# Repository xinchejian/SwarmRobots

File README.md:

xcj_swarm
=========

Xinchejian Swarm Robot project

Introduction:

Build a swarm of robots with autonomus behavior to achieve their goals by interacting with each other using IR communication.

See each xinCheJian wiki for assembly instructions and information.

Original Requirements:
  Each basic robot contains the following:
	- 1x microcontroller Attiny2313
	- 1x motor controller L293D
	- 2x gear motors
	- 1x LiPo battery 3.7V
	Sensor shield

A custom made PCB will be used. This PCB will be mounted into a 3D printed casing which contains the gear motors and the wheels as well the IR sensor array.

Goal is that the maximum price for the basic robot should not exceed 5US$ (without shield)

Each robot will have a basic programming and basic hardware platform. 
The basic programming is:
1. Self protection: 
	- check your battery status
	- find the charging station when battery runs low
	- avoid obstacles and other robots
	- search for power (sunlight etc.)
2. Community (swarm) needs:
	- search for building material
	- search for dead robots
	- bring dead robots to the charging station
	- help dead robots with a charger robot
	- tell others where to find power (sunlight)
	- tell others where is an obstacle or danger

Folder structure:
	/32u4-edwardrf	work in progress - check XCJ mailing list for later versions.
	/AtTiny2313	AtTiny2313 version - that won the AFRON competition
	/ATMEGA328	version based on 
	/ATMEGA168	latest super version (replaces UNO version).

	Note there is a LARGE amount of direct compatability between the code for ALL versions. Differences to note are:
		- different IO pins - see "Arduino, AtTiny, L293 and header pin mappings.ods"
		- size of memory limits size of code
		- AtTiny versions have fewer IO commands available. See http://wiki.xinchejian.com/wiki/Programming-AFRON

Branches & master
	- Please use branches to do YOUR work before committing back to the master!
	- Goal is for the master to be 'production ready' at ALL TIMES!

More at the XinCheJian website wiki.xinchejian.com 
	- the original Swarmrobot pages at http://wiki.xinchejian.com/wiki/Swarm_robots
	- collated summary and AFRON competition entry
	http://wiki.xinchejian.com/wiki/Category:AFRON_$10_Robot_Competition

	latest Swarmrobot index - entry page is now: http://wiki.xinchejian.com/wiki/Category:Swarm_Robots

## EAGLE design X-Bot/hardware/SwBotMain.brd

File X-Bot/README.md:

简介：
   X-Bot是一款群体机器人（Swarm Robot），让这样一群小巧的机器人来实现蚁群可以完成的任务，这就是群体机器人。它由来自新车间（xinchejian.com）创客空间成员组建的一个小组创建。该机器人是基于红外线传感而制作的，它的特点是低成本、易于实践和多功能。该机器人初级版在2012年9月 “AFRON $10 robot challenge” 上获得常规组的第二名。
   该项目有Lutz提议建立，于2012年4月启动，其目的是让成员通过实践可以学到多样的技能，并促进人之间的交流。该目的通过构建个体功能很简单，但通过它们之间的合作可以完成复杂任务的小机器人来实现，这就是Swarm Robot。
该项目在进行中，核心成员为：
   Lutz Michaelis： 德国 （发起人）
   Spencer F：澳大利亚
   Edward Jiang： 中国
   Sunny Sun ：中国
   Leo Yan ： 中国

   在这里归档是LeoYan在其基础上的进一步发展的中级版本，采用了ATMEGA328，拥有更大的创作空间，通过您的加入将会使其功能更完善，也将形成一个圈子，一起交流，一起make stuff。

版权声明：
    所有文档和硬件设计采用：CC BY-NC 3.0 CN ， see <http://creativecommons.net.cn/licenses>
    所有软件代码采用      ：GPL3.0 ，          see <http://www.gnu.org/licenses/>

# English

## Programming

* Checkout and compile the log
 * Set target to Arduino Uno
 * symlink source to SwarmRobot (required by Arduino IDE projects)
* Charge the X-Bot fully
* Configure your X-Bot ID in Swbot.Config.h
 * If you want to start _START_REMOTE_CONTROL
 * Select the behavior you want

```
  #define ROBOT_TYPE_ANT  0x10 (food hunter)
  #define ROBOT_TYPE_ANT_LINEUP 0x11 (line up to and follow the higher id)
  #define ROBOT_TYPE_FOOD 0x21 (turns your X-Bot into a edible source of food)
```
 * Verify the program (compilation step)
* Connect the USB TTL Programmer v2 to your USB
 * Align VCC to VCC
* Upload, should end up with Arduino 1.0.1:

```
avrdude done.  Thank you.
```

## Details

## Behavior changes

In Action.cpp, behavior is defined in RuleTbl as a state machine.

Below, an example using the food hunter behavior:

This represents the current state and the action to do (internal state):

    {INTERIORINFO, TASK_STAGE, TS_LOOKING,  0, 0, 0,  true},

The action is activated under each state by ANYINFO:

    {ANYINFO, 0, 0,  ACTION_IN_SET, TASK_STAGE, TS_LOOKING,  false },

(last boolean is used to create a linked-list of actions to be done following a state)

The first 3 parameters define the conditional for an action... In the case of ANYINFO, there's no conditional so parameters are zero:

    {ANYINFO, 0, 0,  ACTION_EXT_LED, LED_MODE_MANUAL, 0B00,  true},

If the type of message is FOOD, the action is to set the internal variable target to true and keep target id

    {ROBOTINFO_TYPE, ROBOT_ID_ANY, ROBOT_TYPE_FOOD,  ACTION_IN_SET, TARGET, INFO_STATE_SET,  true},

If the TARGET variable is set, then change the state to TS_FOUND:

    {INTERIORINFO, TARGET, INFO_STATE_SET,  ACTION_IN_SET, TASK_STAGE, TS_FOUND,  false},

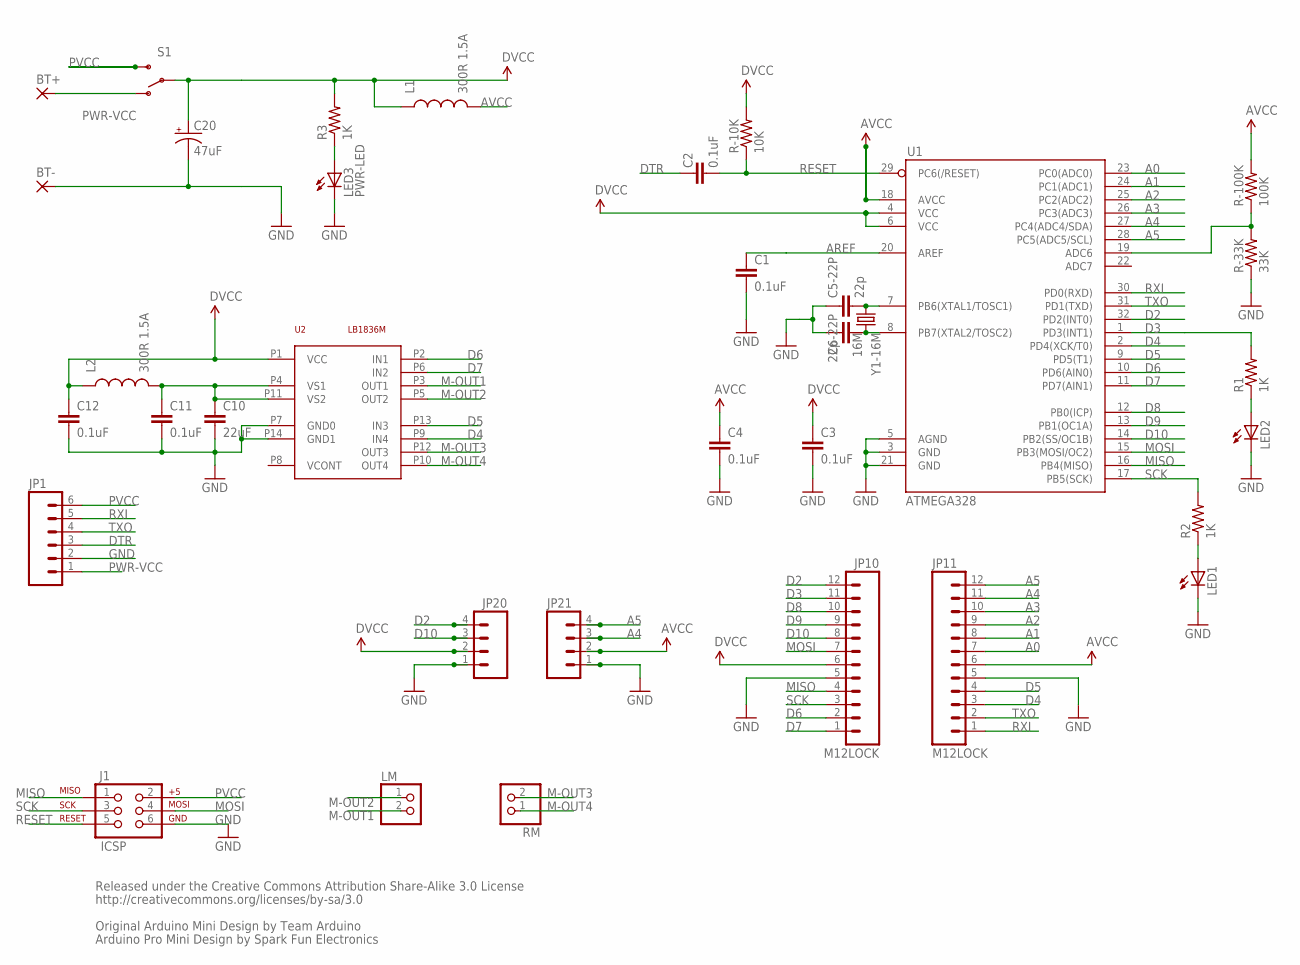
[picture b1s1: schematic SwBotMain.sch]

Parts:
BT+: SMD2; SMD1,27-2,54
BT-: SMD2; SMD1,27-2,54
C1, C2, C3, C4, C11, C12: 0.1uF; 0805
C5-22P, C6-22P: 22p; 0805
C10: 22uF; 1206
C20: 47uF; EIA3528
J1: ICSP; 2X3_LOCK
JP1: M06LOCK; 1X06_LOCK
JP10, JP11: M12LOCK; 1X12_LOCK
JP20, JP21: M04LOCK_LONGPADS; 1X04_LOCK_LONGPADS
L1, L2: 300R 1.5A; 0805
LED1, LED2: LEDCHIP-LED0805; CHIP-LED0805
LED3: PWR-LED; LED5MM
LM: PINHD-1X2; 1X02
R1, R2, R3: 1K; 0805
R-10K: 10K; 0805
R-33K: 33K; 0805
R-100K: 100K; 0805
RM: PINHD-1X2; 1X02
S1: SWITCH-SPDTPTH_LOCK; SWITCH-SPDT_LOCK.007S
U1: ATMEGA328; TQFP32-08
U2: LB1836M; MFP14S
Y1-16M: 16M; CRYSTAL-TXC-7A

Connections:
A0: JP11.7, U1.23 (PC0(ADC0))
A1: JP11.8, U1.24 (PC1(ADC1))
A2: JP11.9, U1.25 (PC2(ADC2))
A3: JP11.10, U1.26 (PC3(ADC3))
A4: JP11.11, JP21.3, U1.27 (PC4(ADC4/SDA))
A5: JP11.12, JP21.4, U1.28 (PC5(ADC5/SCL))
AREF: C1.1, U1.20 (AREF)
AVCC: C4.1, JP11.6, JP21.2, L1.2, R-100K.2, U1.18 (AVCC)
D2: JP10.12, JP20.4, U1.32 (PD2(INT0))
D3: JP10.11, R1.2, U1.1 (PD3(INT1))
D4: JP11.3, U1.2 (PD4(XCK/T0)), U2.P9 (IN4)
D5: JP11.4, U1.9 (PD5(T1)), U2.P13 (IN3)
D6: JP10.2, U1.10 (PD6(AIN0)), U2.P2 (IN1)
D7: JP10.1, U1.11 (PD7(AIN1)), U2.P6 (IN2)
D8: JP10.10, U1.12 (PB0(ICP))
D9: JP10.9, U1.13 (PB1(OC1A))
D10: JP10.8, JP20.3, U1.14 (PB2(SS/OC1B))
DTR: C2.2, JP1.3
DVCC: C3.1, C12.1, C20.A (+), JP10.6, JP20.2, L1.1, L2.1, R3.2, R-10K.2, S1.2, U1.4 (VCC), U1.6 (VCC), U2.P1 (VCC)
GND: BT-.1, C1.2, C3.2, C4.2, C5-22P.1, C6-22P.2, C10.2, C11.2, C12.2, C20.C (-), J1.6, JP1.2, JP10.5, JP11.5, JP20.1, JP21.1, LED1.C, LED2.C, LED3.K (C), R-33K.1, U1.3 (GND), U1.5 (AGND), U1.21 (GND), U2.P7 (GND0), U2.P14 (GND1)
M-OUT1: LM.2, U2.P3 (OUT1)
M-OUT2: LM.1, U2.P5 (OUT2)
M-OUT3: RM.2, U2.P12 (OUT3)
M-OUT4: RM.1, U2.P10 (OUT4)
MISO: J1.1, JP10.4, U1.16 (PB4(MISO))
MOSI: J1.4, JP10.7, U1.15 (PB3(MOSI/OC2))
unnamed: C6-22P.1, U1.8 (PB7(XTAL2/TOSC2)), Y1-16M.P$2 (2)
unnamed: C5-22P.2, U1.7 (PB6(XTAL1/TOSC1)), Y1-16M.P$1 (1)
unnamed: LED2.A, R1.1
unnamed: LED3.A, R3.1
unnamed: C10.1, C11.1, L2.2, U2.P4 (VS1), U2.P11 (VS2)
unnamed: R-33K.2, R-100K.1, U1.19 (ADC6)
unnamed: LED1.A, R2.1
PVCC: J1.2, JP1.6, S1.3 (S)
PWR-VCC: BT+.1, JP1.1, S1.1 (O)
RESET: C2.1, J1.5, R-10K.1, U1.29 (PC6(/RESET))
RXI: JP1.5, JP11.1, U1.30 (PD0(RXD))
SCK: J1.3, JP10.3, R2.2, U1.17 (PB5(SCK))
TXO: JP1.4, JP11.2, U1.31 (PD1(TXD))

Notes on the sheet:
Released under the Creative Commons Attribution Share-Alike 3.0 License
http://creativecommons.org/licenses/by-sa/3.0
Original Arduino Mini Design by Team Arduino
Arduino Pro Mini Design by Spark Fun Electronics

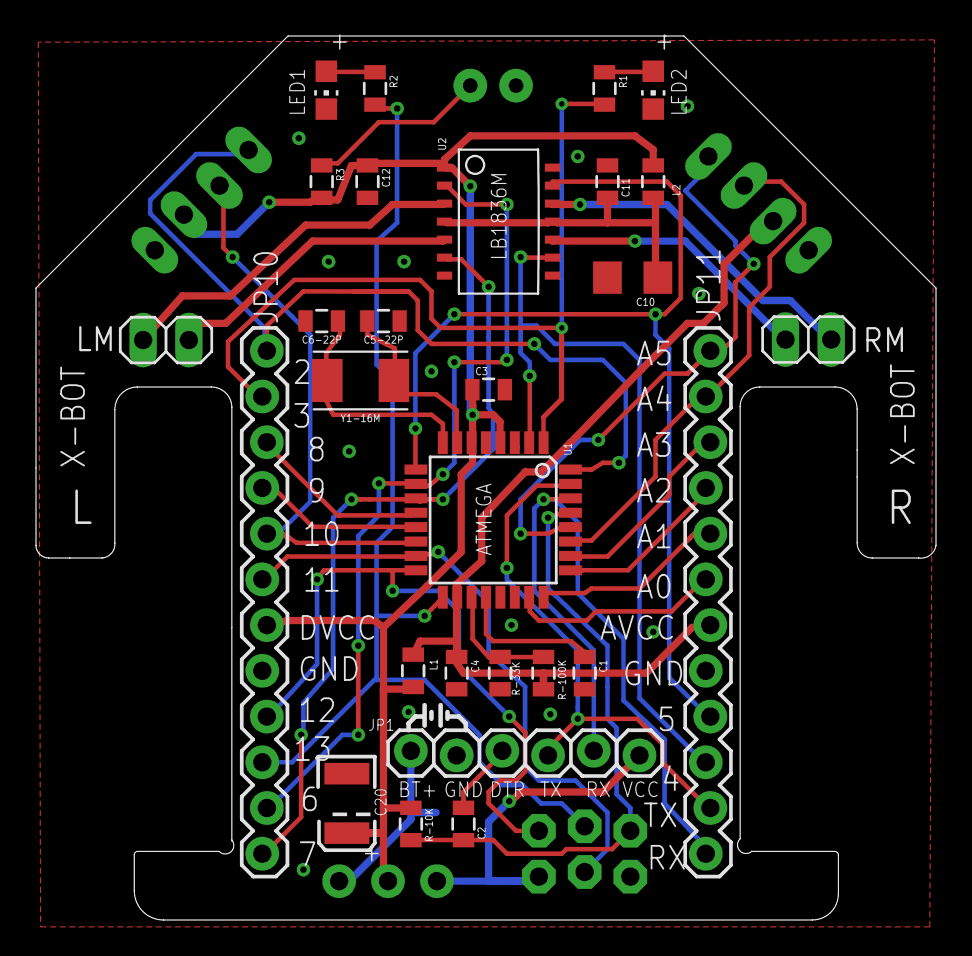
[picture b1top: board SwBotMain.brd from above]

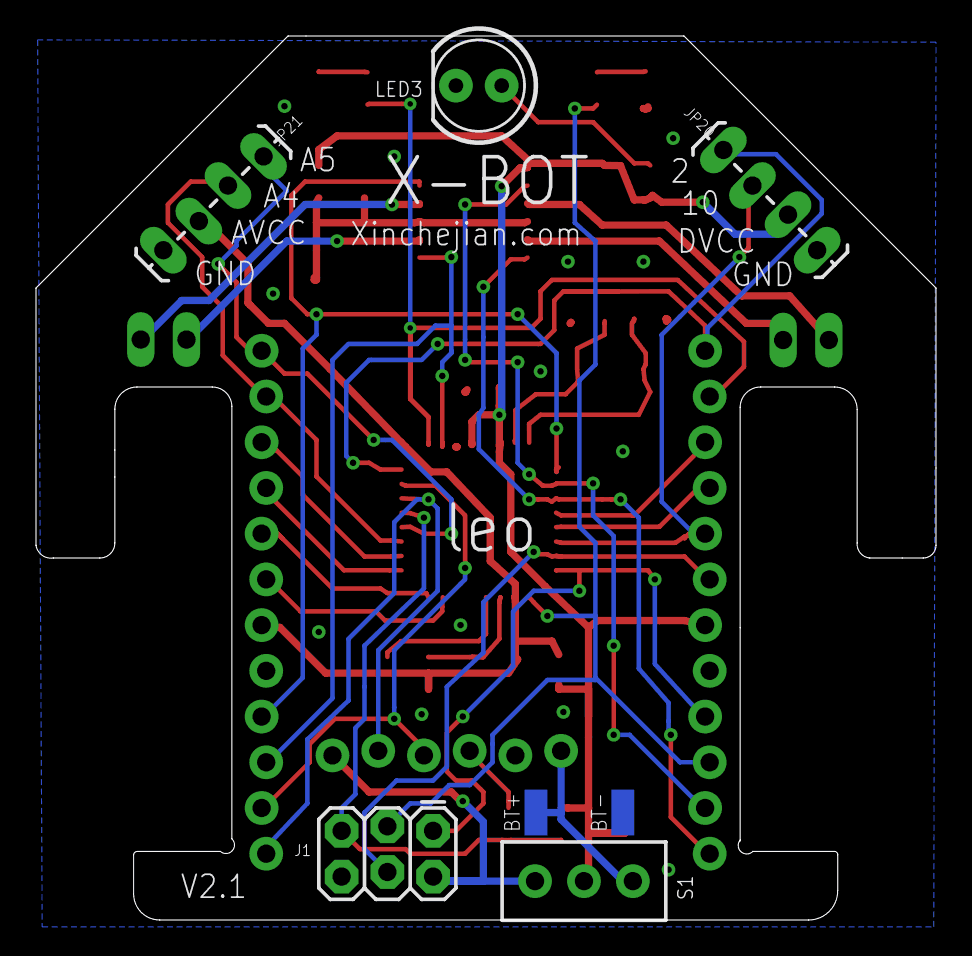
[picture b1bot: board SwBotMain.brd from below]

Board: 2 copper layers, 50.0 x 49.1 mm, 35 parts (7 on the bottom side), 39 nets.

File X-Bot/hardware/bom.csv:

名称;Item;Package;Type;Quantity
MCU;MCU;TQFP;ATMEGA328P-AU;1
电机驱动;MOTOR DRIVER;MFP14S;LB1836M;1
晶振;CRISTAL; EIA3528 (TXC-7A);16M;1
大电流磁珠;Ferrite bead;0805;大电流磁珠 300R 1.5A;2
红外发射管;IR-LED ;5mm;IR-LED;1
一体化红外接收管;IR-RECEIVER ;TSOP;NJL21V400A;4
LED;LED;0805;green;2
LED;LED;0805;orange;4
LED;LED;5mm;red LED 红色;1
排针;Pin header;间距2.54mm 针长12mm;1X40;0.5
排针;Pin header;间距2.54mm  针长12mm;2X40;0.1
排针;Pin header;间距2.54mm;90度 1X40;0.2
排母;Pin socket;2.54mm;1X08;3
排母;Pin socket;2.54mm;1X12;2
电阻;resistor;0805;100K  (1/100precision);1
电阻;resistor;0805;33K (1/100precision);1
电阻;resistor;0805;1k;7
电阻;resistor;0805;150R;2
电阻;resistor;0805;10K;1
电阻;resistor;0805;47R;4
瓷电容;capacitor;0805;0.1uF;6
瓷电容;capacitor;0805;22p;2
瓷电容;capacitor;1206;22uF;5
钽电容;tantalum capacitor;EIA3528;47uF;1
带保护板锂电池;Li Battery ;Larger than 180mA;3cmX2cm;1
小拨动开关;小拨动开关;8mm*4mm 柄5mm;SS-12D0;1
Motor 微型直流减速电机;Motor 微型直流减速电机;;J9xx;2
Screw 平头螺丝;Screw 平头螺丝;;M2*8;2
wheel 皮带轮;wheel 皮带轮;橙色或白色;17*4*1.9;2
垫片;垫片;O型;inter diameter 2.5 mm;2
O型圈密封圈;O型圈密封圈;;外径15，线径2;2
硬纸片;Card board;30mmX30mm; 比如牙膏包装盒，不透光;1

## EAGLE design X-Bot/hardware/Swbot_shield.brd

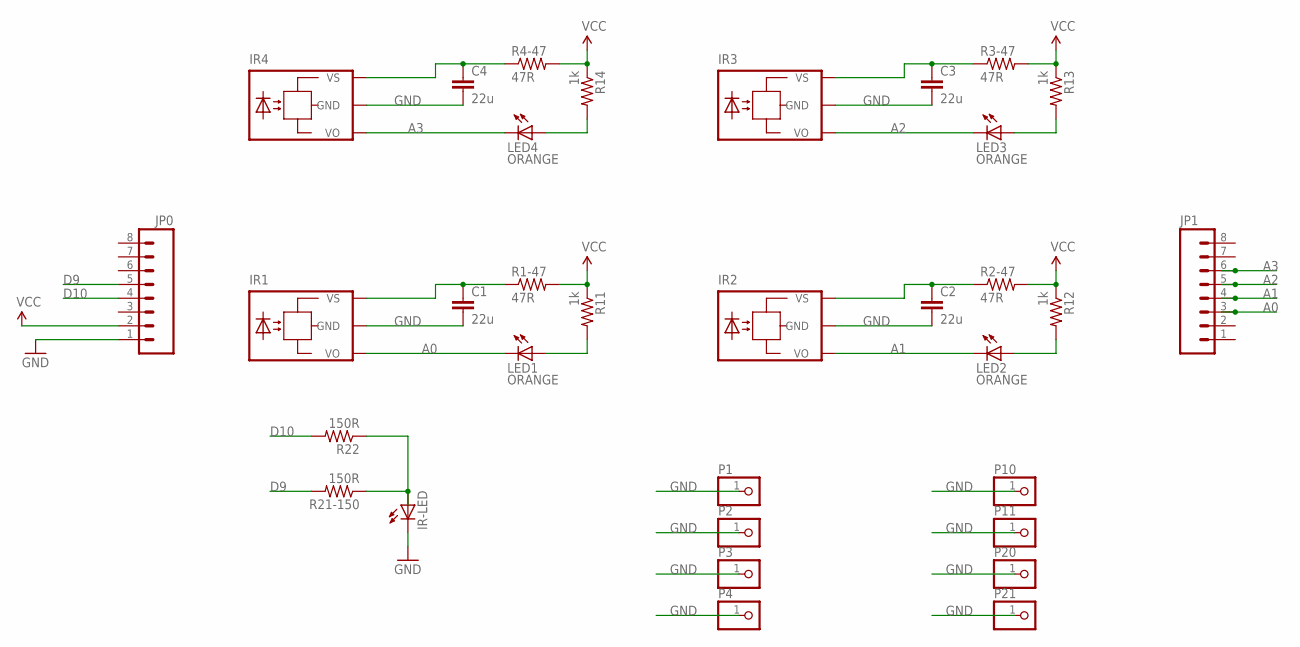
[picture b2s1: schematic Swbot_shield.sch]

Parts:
C1, C2, C3, C4: 22u; 1206
IR1, IR2, IR3, IR4: -NJL; TSOP
IR-LED: LED5MM
JP0, JP1: M08LOCK; 1X08_LOCK
LED1, LED2, LED3, LED4: ORANGE; CHIPLED_0805
P1, P2, P3, P4, P10, P11, P20, P21: PINHD-1X1; 1X01
R1-47, R2-47, R3-47, R4-47: 47R; 0805
R11, R12, R13, R14: 1k; 0805
R21-150, R22: 150R; 0805

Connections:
A0: IR1.VO, JP1.3, LED1.C
A1: IR2.VO, JP1.4, LED2.C
A2: IR3.VO, JP1.5, LED3.C
A3: IR4.VO, JP1.6, LED4.C
D9: JP0.5, R21-150.2
D10: JP0.4, R22.2
GND: C1.2, C2.2, C3.2, C4.2, IR1.GND, IR2.GND, IR3.GND, IR4.GND, IR-LED.K (C), JP0.1, P1.1, P2.1, P3.1, P4.1, P10.1, P11.1, P20.1, P21.1
unnamed: LED1.A, R11.2
unnamed: IR-LED.A, R21-150.1, R22.1
unnamed: LED2.A, R12.2
unnamed: LED3.A, R13.2
unnamed: C2.1, IR2.VCC (VS), R2-47.1
unnamed: LED4.A, R14.2
unnamed: C4.1, IR4.VCC (VS), R4-47.1
unnamed: C3.1, IR3.VCC (VS), R3-47.1
unnamed: C1.1, IR1.VCC (VS), R1-47.1
VCC: JP0.2, R1-47.2, R2-47.2, R3-47.2, R4-47.2, R11.1, R12.1, R13.1, R14.1

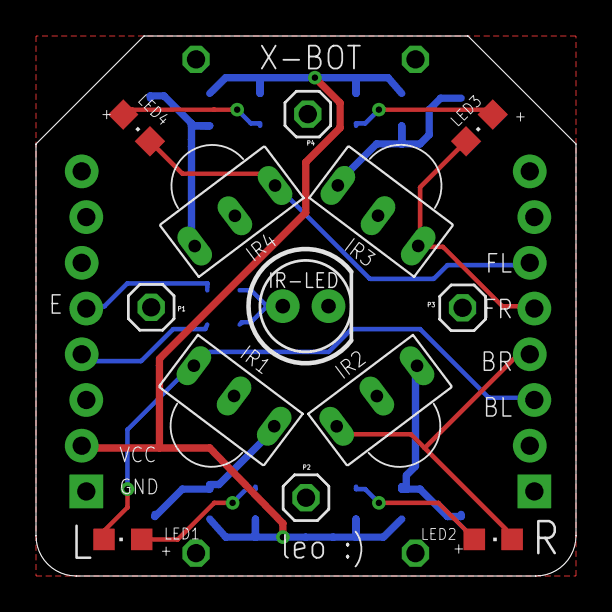
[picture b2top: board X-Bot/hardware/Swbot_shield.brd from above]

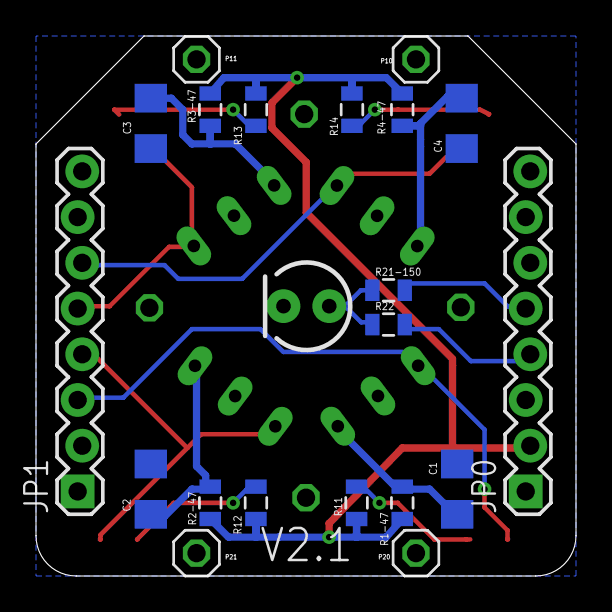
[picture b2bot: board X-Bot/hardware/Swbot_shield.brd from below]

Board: 2 copper layers, 30.0 x 30.0 mm, 33 parts (20 on the bottom side), 17 nets.

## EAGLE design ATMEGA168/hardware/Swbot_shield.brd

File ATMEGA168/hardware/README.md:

xcj_swarm
=========

Xinchejian Swarm Robot project

Introduction:

Build a swarm of robots with autonomus behavior to achieve their goals by interacting with each other using IR communication.

Requirements:

Each basic robot contains the following:
	
	- 1x microcontroller Attiny2313
	- 1x motor controller L293D
	- 2x gear motors
	- 1x LiPo battery 3.7V
	Sensor shield

A custom made PCB will be used. This PCB will be mounted into a 3D printed casing which contains the gear motors and the wheels as well the IR sensor array.

Goal is that the maximum price for the basic robot should not exceed 5US$ (without shield)

Each robot will have a basic programming and basic hardware platform. 
The basic programming is:

1. Self protection: 
	- check your battery status
	- find the charging station when battery runs low
	- avoid obstacles and other robots
	- search for power (sunlight etc.)
2. Community (swarm) needs:
	- search for building material
	- search for dead robots
	- bring dead robots to the charging station
	- help dead robots with a charger robot
	- tell others where to find power (sunlight)
	- tell others where is an obstacle or danger

Folder structure:

	/kicad 		AtTin2313 - kicad schematics and PCB design files
	/source		AtTin2313 - source code

	/ATMEGA328	version based on 
	/UNO		version built onto and existing Arduino UNO.

	Note there is a LARGE amount of direct compatability between the code for ALL versions. Differences to note are:
		- different IO pins - see "Arduino, AtTiny, L293 and header pin mappings.ods"
		- size of memory limits size of code
		- AtTiny versions have fewer IO commands available. See http://wiki.xinchejian.com/wiki/Programming-AFRON

Branches & master
	- Please use branches to do YOUR work before committing back to the master!
	- Goal is for the master to be 'production ready' at ALL TIMES!

Sample Git info:
    http://kentnguyen.com/development/visualized-git-practices-for-team/
    http://gitref.org/branching/
    http://marklodato.github.com/visual-git-guide/index-en.html
    http://think-like-a-git.net/
    https://github.com/diaspora/diaspora/wiki/Git-Workflow

More at the XinCheJian website wiki.xinchejian.com 
	- the original Swarmrobot pages at http://wiki.xinchejian.com/wiki/Swarm_robots
	- collated summary and AFRON competition entry
		 - URL not yet published, but after 15/9/2012 you will find it via 
				http://wiki.xinchejian.com/wiki/Category:AFRON_$10_Robot_Competition

************************************************************
Changes made to move from previous mess to this structure:-

/swarmIR		-> AtTiny2313/hardware/swarmIRShield
/kicad			-> AtTiny2313/hardware/mainPCB

/source-Avoid-Follow	-> AtTiny2313/software/SwitchShield_Avoid_Follow 
/source-IR		-> AtTiny2313/software/IR_Follow_AFRON
/swarm_wall_follow_ir	-> AtTiny2313/software/IR_object_detection

All the Arduino code files also renamed so can open sketches in the folder!

************************************************************

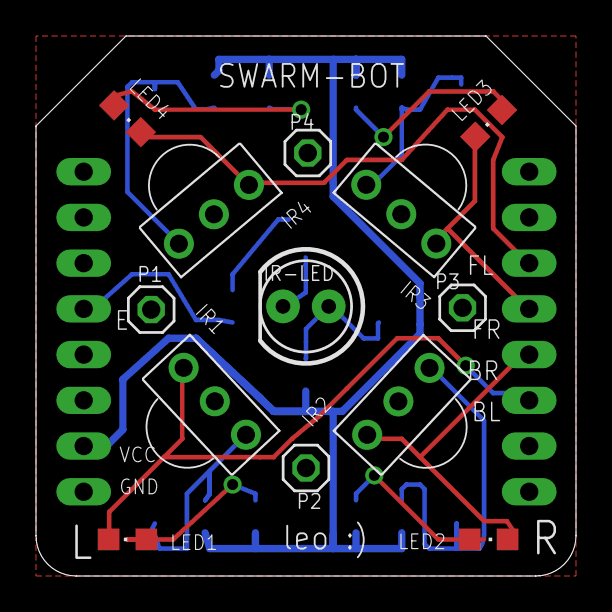
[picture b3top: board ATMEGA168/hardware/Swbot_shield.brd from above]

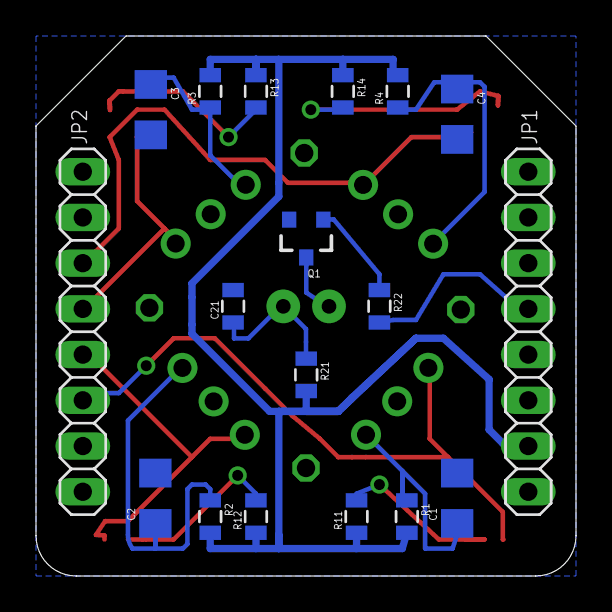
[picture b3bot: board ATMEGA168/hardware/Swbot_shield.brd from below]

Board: 2 copper layers, 30.0 x 30.0 mm, 31 parts (18 on the bottom side), 18 nets.

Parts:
C1, C2, C3, C4: 22u; 1206
C21: 0.1u; 0805
IR1, IR2, IR3, IR4: TSOP
IR-LED: LED5MM
JP1, JP2: 1X08
LED1, LED2, LED3, LED4: ORANGE; CHIPLED_0805
P1, P2, P3, P4: 1X01
Q1: S9013; SOT23-3
R1, R2, R3, R4, R21: 47R; 0805
R11, R12, R13, R14: 1k; 0805
R22: 220R; 0805

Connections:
A0: IR1.VO, JP2.3, LED1.C
A1: IR2.VO, JP2.4, LED2.C
A2: IR3.VO, JP2.5, LED3.C
A3: IR4.VO, JP2.6, LED4.C
D9: JP1.5, R22.2
GND: C1.2, C2.2, C3.2, C4.2, C21.2, IR1.GND, IR2.GND, IR3.GND, IR4.GND, JP1.1, P1.1, P2.1, P3.1, P4.1, Q1.2
unnamed: LED1.A, R11.2
unnamed: C21.1, IR-LED.A, R21.1
unnamed: IR-LED.K, Q1.3
unnamed: LED2.A, R12.2
unnamed: Q1.1, R22.1
unnamed: LED3.A, R13.2
unnamed: C2.1, IR2.VCC, R2.1
unnamed: LED4.A, R14.2
unnamed: C4.1, IR4.VCC, R4.1
unnamed: C3.1, IR3.VCC, R3.1
unnamed: C1.1, IR1.VCC, R1.1
VCC: JP1.2, R1.2, R2.2, R3.2, R4.2, R11.1, R12.1, R13.1, R14.1, R21.2

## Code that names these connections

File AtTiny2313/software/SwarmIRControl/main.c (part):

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#endif

// These pins receive signals from the IR LEDs
#define IR_FC PD4              // IR LED Front Center
#define IR_R  PB0              // IR LED Rear
#define IR_FL PD6              // IR LED Front Left
#define IR_FR PB1              // IR LED Front Right



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#define IR_PIN PIND
int irPINIndex = 0;

//#define IR_IN  PD6             // Pin used for IR RC5 decode - using seperate (duplicate) definition to above - so can easily change!
//#define IR_PIN PIND            // port of pin above - used in IR decode function

/* All AtTiny2313 pins used for IR Rx

    *** take great care in the code!!!!- 1st two on portD, 2nd 2 on PortB

D6	8	PD4	P2 3	IR_FC
D8	11	PD6	P2 6	IR_FL

D9	12	PB0	P2 5	IR_R
D10	13	PB1	P2 4	IR_FR
*/



#define FLASHLED
#ifdef FLASHLED
    #define RX   PD0
    #define TX   PD1
#endif


// temp debug - do not use this AND FLASHLED!!!!!!
//#define CMD_FLASHLED
#ifdef CMD_FLASHLED
    #define RX   PD0
    #define TX   PD1
#endif


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//Motor pin definitions
#define M_LF PA1             // Motor Left Front
#define M_LB PA0             // Motor Left Back
#define M_RF PD2             // Motor Right Front
#define M_RB PD3             // Motor Right Back

#define M_REn PD5            // Motor Right Enable
#define M_LEn PB2            // Motor Left Enable

#define ROBOT_CMD_MASK  0x3F
#define ROBOT_SYS_MASK  0x1F
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
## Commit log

2012-08-08 Initial schematics, PCBs & code from Edward
2012-08-08 Added Edwards notes to IR2
2012-08-08 Added pdf & jpg of schematic & PCB
2012-08-08 Added some documentation to soccerbot_IR1.ino
2012-08-09 Added Summary of Kicad schematic & PCB files.txt
2012-08-09 Added simple schematic of IR shield
2012-08-09 Added simple schematic of IR shield pdf
2012-08-09 My test file to push
2012-08-09 test file deleted
2012-08-09 add edward's version of routed prototype which sent for printing
2012-08-10 updated: Summary of Kicad schematic & PCB files.txt
2012-08-11 Added: kicad/IR Shield pinouts v0.1.txt
2012-08-11 moved all old ones to the folder trash
2012-08-13 Added pdf of PCB sent to manufacturing
2012-08-19 Added pin mapping spreadsheet and updated code to match the new PCBs
2012-08-29 breaking shit
2012-08-30 Beautifed code & doco, added spin & turn, reverted Spanner's non working code
2012-09-11 tidyup - deleted all kicad/* except edward_version, updated readme.md & Summary of Kicad schematic & PCB files.txt
2012-09-11 hopefully now actually deleting the files
2012-09-11 Moving Edwards files used to manufacture to /kicad, deleting remainder
2012-09-11 added Atmega & uno folders, deleted WIP PWM code (will put in branch)
2012-09-11 updated readme about branching
2012-09-11 renamed source dir to source IR
2012-09-11 Remove duplicated directory
2012-09-11 added source-Avoid-Follow
2012-09-12 1.Code for IR-Swarmbot at source directory. The PWM library is used, so you must install the lib. 2.SoftDesign.dia should be opened by DIA software which can be download from ubuntu software center. 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
2012-09-12 Add the IR shield for swarm robot.
2012-09-13 added jpg of all scehmatics & PCBs
2012-09-13 tidy up header & licence information
2012-09-13 IR shield PCB and notes for the new mainboard
2012-09-15 added Pricing spreadsheet
2012-09-18 updating most Tadobao link styles due to expiry
2012-09-19 to fix the bug of line 106
2012-09-21 Simple code to use the IR shield to detect surroundings.
2012-09-21 add some comments
2012-10-12 restoring missing attiny.lib
2012-10-12 added pullups, filter cap & series R
2012-10-12 added 2 more IR Rx & pullups
2012-10-13 routed board & updated pin map spreadsheet
2012-10-13 Added 2xIR receivers, 6xpullups, filter capacitor, series R, header breakout pads
2012-10-13 Some local changes
2012-10-15 Added simple motor control, startup LED indication, code annotation, left lots of test code {commented out}
2012-10-15 basic avoid logic - used in video
2012-10-17 Update the IR shield design.
2012-10-18 fixed unconencted pin on R6 in schematic
2012-10-22 Working RC5 IR control & start of moving ALL AtTiny2313 files to /atTiny2313/hardware & /software directories
2012-10-22 Move all AtTiny hardware & software directories from root to /AtTiny2313
2012-10-22 ... now removing the old directories from repo root
2012-10-24 Added Swarm_Random_Demo & updated atTiny2313/readme.md
2012-10-25 Added Group control via switches to SwarmIRControl & SwarmIRControlArduino
2012-10-26 AtTiny2313/MotorTest - so it is easy wire BOTH motors up corectly
2012-10-26 Added code comments 4/8MHz fuses, updated IR shield graphics
2012-11-01 Updated IR RC5 decoding & added demo mode
2012-11-01 minor group 0 bug fix
2012-11-08 Add PCB design file.
2012-11-08 Change UNO to ATMEGA168. Add hardware to it.
2012-11-16 SwarmRobot presentation
2012-11-25 updated readme.MD files
2013-01-06 add bootloader of 12m crystal
2013-01-06 X-Bot V2.1 alpha
2013-01-25 Add near detecting. and locate relative position with each other. add Ricky request
2013-01-25 update Manual
2013-02-10 Add new roles: Line up, keep similiar direction, The Earth circle around the Sun.

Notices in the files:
parts and their libraries:
SparkFun-Connectors: Licensing: CC v3.0 Share-Alike You are welcome to use this library for commercial purposes.
